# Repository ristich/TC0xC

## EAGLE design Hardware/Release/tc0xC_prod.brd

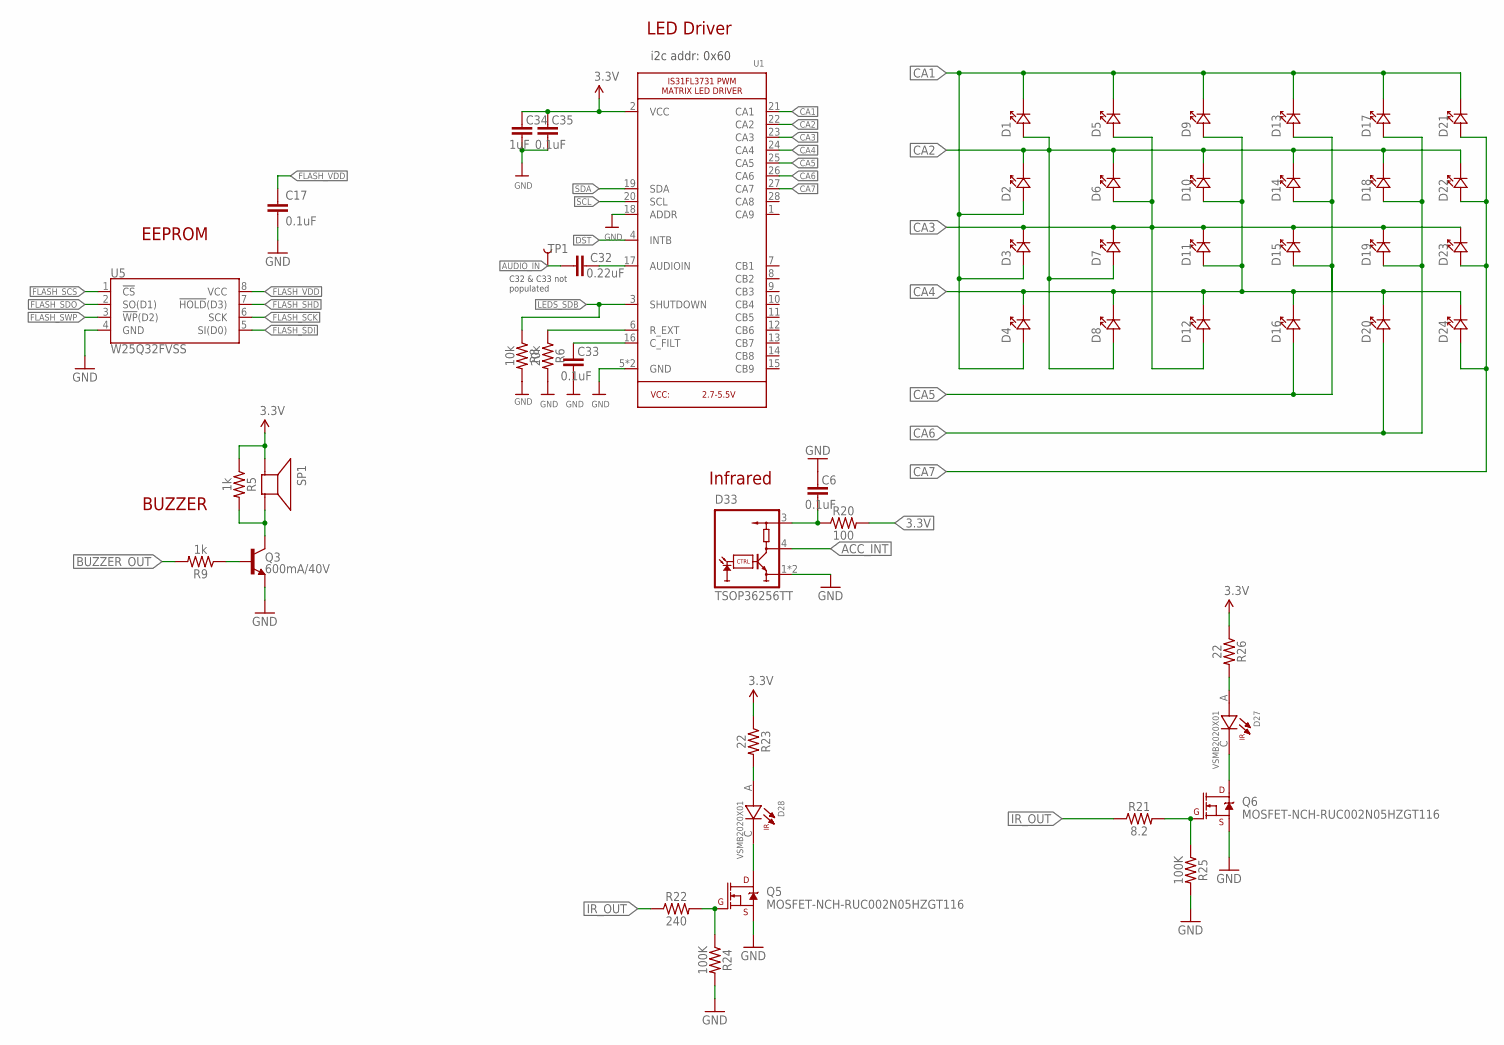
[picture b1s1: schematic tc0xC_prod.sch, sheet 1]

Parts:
C6, C17, C33, C35: 0.1uF; 0603
C32: 0.22uF; 0603
C34: 1uF; 0603
D1, D2, D3, D4, D5, D6, D7, D8, D9, D10, D11, D12, D13, D14, D15, D16, D17, D18, D19, D20, D21, D22, D23, D24: LED-603; SMD-603
D27, D28: VSMB2020X01; DIO_VSMB2020X01
D33: TSOP36256TT; TSOP36256
Q3: 600mA/40V; SOT23-3
Q5, Q6: MOSFET-NCH-RUC002N05HZGT116; SOT-23-3
R5, R9: 1k; 0603
R6: 20k; 0603
R8: 10k; 0603
R20: 100; 0603
R21: 8.2; 0603
R22: 240; 0603
R23, R26: 22; 0603
R24, R25: 100K; 0603
SP1: SPEAKER/PS12; PS12
TP1: TEST-POINT3X5; PAD.03X.05
U1: IS31FL3731QFN; QFN-28_4MM_0.4MM
U5: W25Q32FVSS; SOIC-8

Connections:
3.3V: C34.1, C35.1, R5.1, R20.2, R23.1, R26.1, SP1.P$1 (+), U1.2 (VCC); also elsewhere on the board
ACC_INT: D33.4 (OUT); also elsewhere on the board
AUDIO_IN: C32.1, TP1.P$1
BUZZER_OUT: R9.2; also elsewhere on the board
CA1: D1.P$2 (CATHODE-), D2.P$1 (ANODE+), D3.P$1 (ANODE+), D4.P$1 (ANODE+), D5.P$2 (CATHODE-), D9.P$2 (CATHODE-), D13.P$2 (CATHODE-), D17.P$2 (CATHODE-), D21.P$2 (CATHODE-), U1.21 (CA1)
CA2: D1.P$1 (ANODE+), D2.P$2 (CATHODE-), D6.P$2 (CATHODE-), D7.P$1 (ANODE+), D8.P$1 (ANODE+), D10.P$2 (CATHODE-), D14.P$2 (CATHODE-), D18.P$2 (CATHODE-), D22.P$2 (CATHODE-), U1.22 (CA2)
CA3: D3.P$2 (CATHODE-), D5.P$1 (ANODE+), D6.P$1 (ANODE+), D7.P$2 (CATHODE-), D11.P$2 (CATHODE-), D12.P$1 (ANODE+), D15.P$2 (CATHODE-), D19.P$2 (CATHODE-), D23.P$2 (CATHODE-), U1.23 (CA3)
CA4: D4.P$2 (CATHODE-), D8.P$2 (CATHODE-), D9.P$1 (ANODE+), D10.P$1 (ANODE+), D11.P$1 (ANODE+), D12.P$2 (CATHODE-), D16.P$2 (CATHODE-), D20.P$2 (CATHODE-), D24.P$2 (CATHODE-), U1.24 (CA4)
CA5: D13.P$1 (ANODE+), D14.P$1 (ANODE+), D15.P$1 (ANODE+), D16.P$1 (ANODE+), U1.25 (CA5)
CA6: D17.P$1 (ANODE+), D18.P$1 (ANODE+), D19.P$1 (ANODE+), D20.P$1 (ANODE+), U1.26 (CA6)
CA7: D21.P$1 (ANODE+), D22.P$1 (ANODE+), D23.P$1 (ANODE+), D24.P$1 (ANODE+), U1.27 (CA7)
DST: U1.4 (INTB); also elsewhere on the board
FLASH_SCK: U5.6 (SCK); also elsewhere on the board
FLASH_SCS: U5.1 (!CS!); also elsewhere on the board
FLASH_SDI: U5.5 (SI(D0)); also elsewhere on the board
FLASH_SDO: U5.2 (SO(D1)); also elsewhere on the board
FLASH_SHD: U5.7 (!HOLD!(D3)); also elsewhere on the board
FLASH_SWP: U5.3 (!WP!(D2)); also elsewhere on the board
FLASH_VDD: C17.1, U5.8 (VCC); also elsewhere on the board
GND: C6.1, C17.2, C33.2, C34.2, C35.2, D33.1 (GND), D33.2 (GND), Q3.2 (E), Q5.2 (S), Q6.2 (S), R6.2, R8.2, R24.2, R25.2, U1.5 (GND), U1.18 (ADDR), U1.THERMAL (GND), U5.4 (GND); also elsewhere on the board
IR_OUT: R21.1, R22.1; also elsewhere on the board
LEDS_SDB: R8.1, U1.3 (SHUTDOWN); also elsewhere on the board
unnamed: C33.1, U1.16 (C_FILT)
unnamed: R6.1, U1.6 (R_EXT)
unnamed: Q3.3 (C), R5.2, SP1.P$2 (-)
unnamed: Q6.1 (G), R21.2, R25.1
unnamed: Q5.1 (G), R22.2, R24.1
unnamed: C32.2, U1.17 (AUDIOIN)
unnamed: C6.2, D33.3 (VS), R20.1
unnamed: D28.C, Q5.3 (D)
unnamed: D28.A, R23.2
unnamed: D27.C, Q6.3 (D)
unnamed: D27.A, R26.2
unnamed: Q3.1 (B), R9.1
SCL: U1.20 (SCL); also elsewhere on the board
SDA: U1.19 (SDA); also elsewhere on the board

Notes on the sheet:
i2c addr: 0x60
C32 & C33 not populated
EEPROM
BUZZER
LED Driver
Infrared

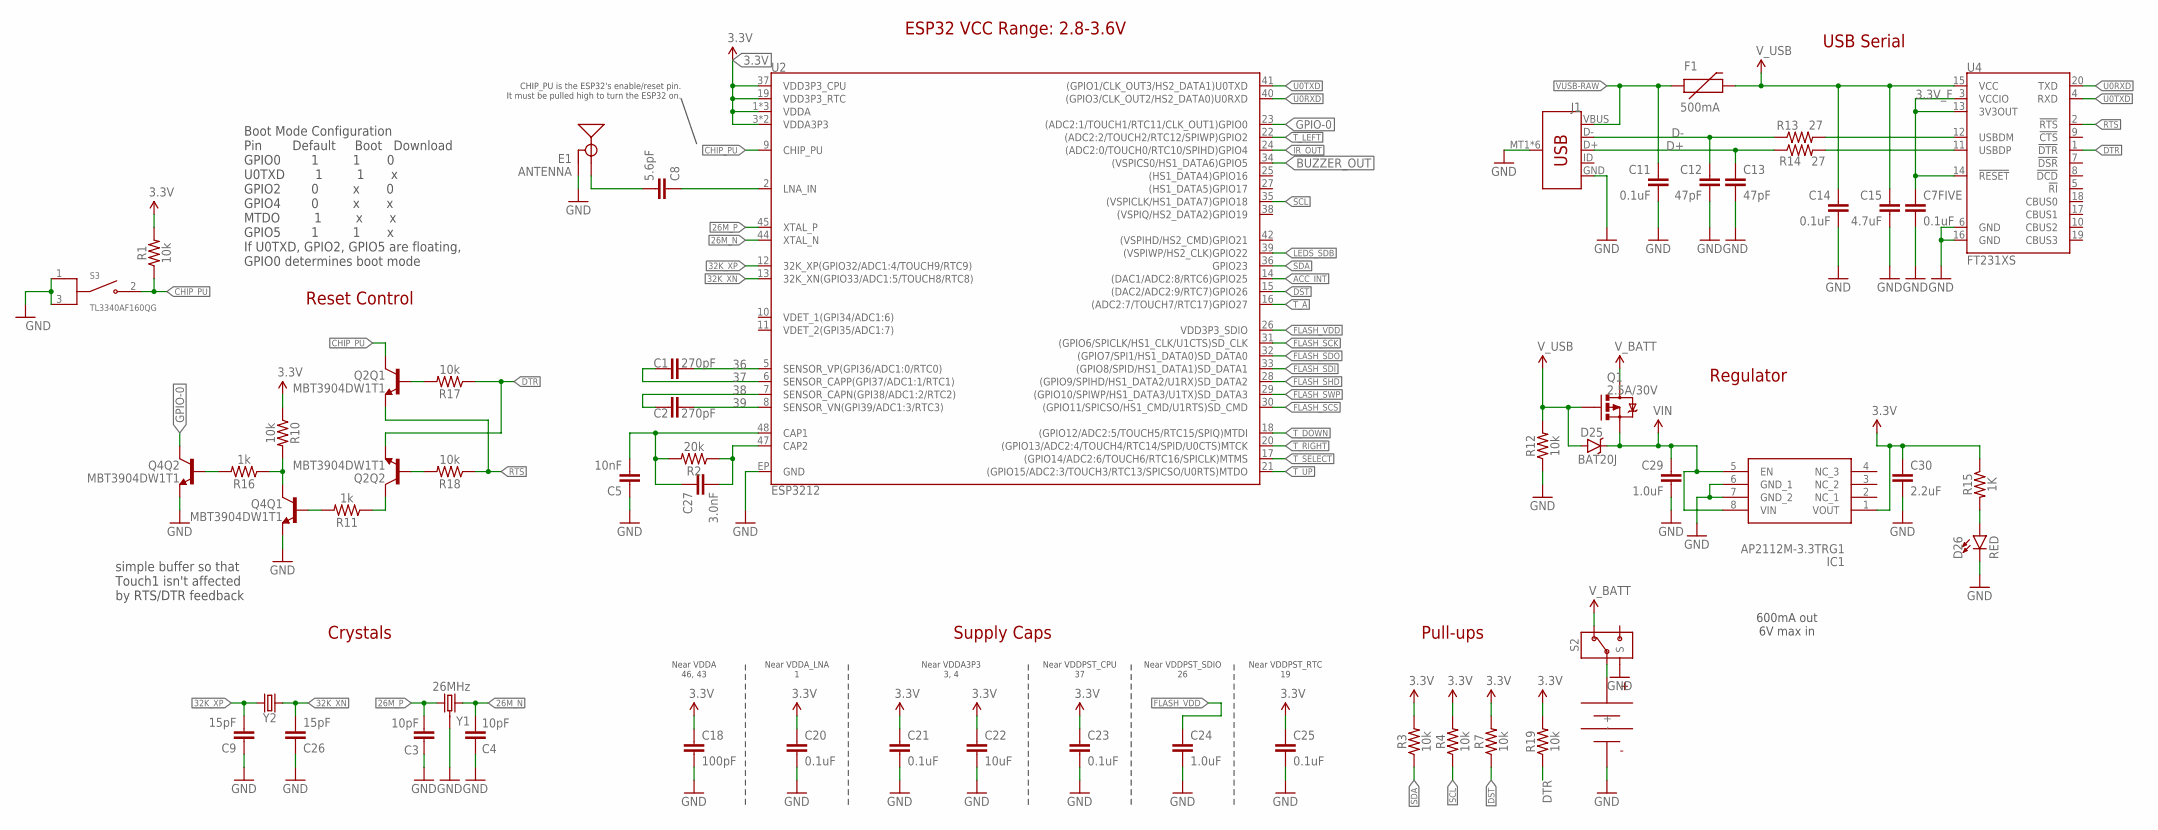
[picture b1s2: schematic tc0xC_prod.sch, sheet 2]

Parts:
C1, C2: 270pF; 0603
C3, C4: 10pF; 0603
C5: 10nF; 0603
C7FIVE, C11, C14, C20, C21, C23, C25: 0.1uF; 0603
C8: 5.6pF; 0603
C9, C26: 15pF; 0603
C12, C13: 47pF; 0603
C15: 4.7uF; 0603
C18: 100pF; 0603
C22: 10uF; 0603
C24: 1.0uF; 0603
C27: 3.0nF; 0603
C29: 1.0uF; 0805
C30: 2.2uF; 0603
D25: BAT20J; SOD-323
D26: RED; LED-0603@1
E1: ANTENNA; TRACE_ANTENNA_2.4GHZ_25.7MM_TUNED
F1: 500mA; PTC-1206
G2: KEYSTONE_2479
IC1: AP2112M-3.3TRG1; SOIC127P600X170-8N
J1: USB_MICRO-B; USB-MICROB-10118192
Q1: 2.5A/30V; SOT23-3@1
Q2, Q4: MBT3904DW1T1; SC70-6
R1, R3, R4, R7, R10, R12, R17, R18, R19: 10k; 0603
R2: 20k; 0603
R11, R16: 1k; 0603
R13, R14: 27; 0603
R15: 1K; 0603
S2: CUS-12B; CUS-12_SPDT
S3: TL3340AF160QG; SW_TL3340AF160QG
U2: ESP3212; QFN48-0.4MM
U4: FT231XS; SSOP20_L
Y1: 26MHz; CRYSTAL-SMD-3.2X2.5
Y2: 32.768kHz; FC-12M

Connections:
3.3V: C18.1, C20.1, C21.1, C22.1, C23.1, C25.1, C30.1, IC1.1 (VOUT), R1.2, R3.2, R4.2, R7.2, R10.1, R15.1, R19.2, U2.1 (VDDA), U2.3 (VDDA3P3), U2.4 (VDDA3P3), U2.19 (VDD3P3_RTC), U2.37 (VDD3P3_CPU), U2.43 (VDDA), U2.46 (VDDA); also elsewhere on the board
3.3V_F: C7FIVE.1, U4.3 (VCCIO), U4.13 (3V3OUT), U4.14 (!RESET)
26M_N: C4.2, U2.44 (XTAL_N), Y1.3 (2)
26M_P: C3.2, U2.45 (XTAL_P), Y1.1
32K_XN: C26.2, U2.13 (32K_XN(GPIO33/ADC1:5/TOUCH8/RTC8)), Y2.2
32K_XP: C9.2, U2.12 (32K_XP(GPIO32/ADC1:4/TOUCH9/RTC9)), Y2.1
36: C1.2, U2.5 (SENSOR_VP(GPI36/ADC1:0/RTC0))
37: C1.1, U2.6 (SENSOR_CAPP(GPI37/ADC1:1/RTC1))
38: C2.1, U2.7 (SENSOR_CAPN(GPI38/ADC1:2/RTC2))
39: C2.2, U2.8 (SENSOR_VN(GPI39/ADC1:3/RTC3))
ACC_INT: U2.14 ((DAC1/ADC2:8/RTC6)GPIO25); also elsewhere on the board
BUZZER_OUT: U2.34 ((VSPICS0/HS1_DATA6)GPIO5); also elsewhere on the board
CAP_10N: C5.2, C27.1, R2.2, U2.48 (CAP1)
CHIP_PU: Q2.3 (C), R1.1, S3.2 (NO), U2.9 (CHIP_PU)
D+: C13.1, J1.D+, R14.1
D-: C12.1, J1.D-, R13.1
DST: R7.1, U2.15 ((DAC2/ADC2:9/RTC7)GPIO26); also elsewhere on the board
DTR: Q2.1 (E), R17.1, R19.1, U4.1 (!DTR)
FLASH_SCK: U2.31 ((GPIO6/SPICLK/HS1_CLK/U1CTS)SD_CLK); also elsewhere on the board
FLASH_SCS: U2.30 ((GPIO11/SPICSO/HS1_CMD/U1RTS)SD_CMD); also elsewhere on the board
FLASH_SDI: U2.33 ((GPIO8/SPID/HS1_DATA1)SD_DATA1); also elsewhere on the board
FLASH_SDO: U2.32 ((GPIO7/SPI1/HS1_DATA0)SD_DATA0); also elsewhere on the board
FLASH_SHD: U2.28 ((GPIO9/SPIHD/HS1_DATA2/U1RX)SD_DATA2); also elsewhere on the board
FLASH_SWP: U2.29 ((GPIO10/SPIWP/HS1_DATA3/U1TX)SD_DATA3); also elsewhere on the board
FLASH_VDD: C24.1, U2.26 (VDD3P3_SDIO); also elsewhere on the board
GND: C3.1, C4.1, C5.1, C7FIVE.2, C9.1, C11.2, C12.2, C13.2, C14.2, C15.2, C18.2, C20.2, C21.2, C22.2, C23.2, C24.2, C25.2, C26.1, C29.2, C30.2, D26.C, E1.GND, E1.GND2 (GND), G2.-, IC1.6 (GND_1), IC1.7 (GND_2), J1.GND, J1.MT1 (SHIELD), J1.MT2 (SHIELD), J1.MT3 (SHIELD), J1.MT4 (SHIELD), J1.P$1 (SHIELD), J1.P$2 (SHIELD), Q4.1 (E), Q4.4 (E), R12.1, S2.P$4 (S), S2.P$5 (S), S2.P$6 (S), S2.P$7 (S), S3.1 (COM_1), S3.3 (COM_2), U2.EP (GND), U4.6 (GND), U4.16 (GND), Y1.2 (GND), Y1.4 (GND); also elsewhere on the board
GPIO-0: Q4.6 (C), U2.23 ((ADC2:1/TOUCH1/RTC11/CLK_OUT1)GPIO0)
IR_OUT: U2.24 ((ADC2:0/TOUCH0/RTC10/SPIHD)GPIO4); also elsewhere on the board
LEDS_SDB: U2.39 ((VSPIWP/HS2_CLK)GPIO22); also elsewhere on the board
LNA_IN: C8.1, U2.2 (LNA_IN)
unnamed: C27.2, R2.1, U2.47 (CAP2)
unnamed: R13.2, U4.12 (USBDM)
unnamed: R14.2, U4.11 (USBDP)
unnamed: Q4.2 (B), R16.2
unnamed: Q2.5 (B), R17.2
unnamed: Q2.2 (B), R18.2
unnamed: Q4.3 (C), R10.2, R16.1
unnamed: Q4.5 (B), R11.2
unnamed: Q2.6 (C), R11.1
unnamed: G2.+, S2.P$2 (1)
unnamed: D26.A, R15.2
RTS: Q2.4 (E), R18.1, U4.2 (!RTS)
SCL: R4.1, U2.35 ((VSPICLK/HS1_DATA7)GPIO18); also elsewhere on the board
SDA: R3.1, U2.36 (GPIO23); also elsewhere on the board
TRACE_ANT: C8.2, E1.ANT (SIGNAL)
T_A: U2.16 ((ADC2:7/TOUCH7/RTC17)GPIO27)
T_DOWN: U2.18 ((GPIO12/ADC2:5/TOUCH5/RTC15/SPIQ)MTDI)
T_LEFT: U2.22 ((ADC2:2/TOUCH2/RTC12/SPIWP)GPIO2)
T_RIGHT: U2.20 ((GPIO13/ADC2:4/TOUCH4/RTC14/SPID/U0CTS)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)
T_SELECT: U2.17 ((GPIO14/ADC2:6/TOUCH6/RTC16/SPICLK)MTMS)
T_UP: U2.21 ((GPIO15/ADC2:3/TOUCH3/RTC13/SPICSO/U0RT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)
U0RXD: U2.40 ((GPIO3/CLK_OUT2/HS2_DATA0)U0RXD), U4.20 (TXD)
U0TXD: U2.41 ((GPIO1/CLK_OUT3/HS2_DATA1)U0TXD), U4.4 (RXD)
VIN: C29.1, D25.C, IC1.5 (EN), IC1.8 (VIN), Q1.2 (S)
VUSB-RAW: C11.1, F1.1, J1.VBUS
V_BATT: Q1.3 (D), S2.P$1 (2)
V_USB: C14.1, C15.1, D25.A, F1.2, Q1.1 (G), R12.2, U4.15 (VCC)

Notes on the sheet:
Near VDDA 46, 43
Near VDDA_LNA 1
Near VDDA3P3 3, 4
Near VDDPST_CPU 37
Near VDDPST_SDIO 26
Near VDDPST_RTC 19
ESP32 VCC Range: 2.8-3.6V
CHIP_PU is the ESP32's enable/reset pin. It must be pulled high to turn the ESP32 on.
Supply Caps
Reset Control
Crystals
600mA out 6V max in
Regulator
USB Serial
Boot Mode Configuration Pin Default Boot Download GPIO0 1 1 0 U0TXD 1 1 x GPIO2 0 x 0 GPIO4 0 x x MTDO 1 x x GPIO5 1 1 x If U0TXD, GPIO2, GPIO5 are floating, GPIO0 determines boot mode
Pull-ups
simple buffer so that Touch1 isn't affected by RTS/DTR feedback

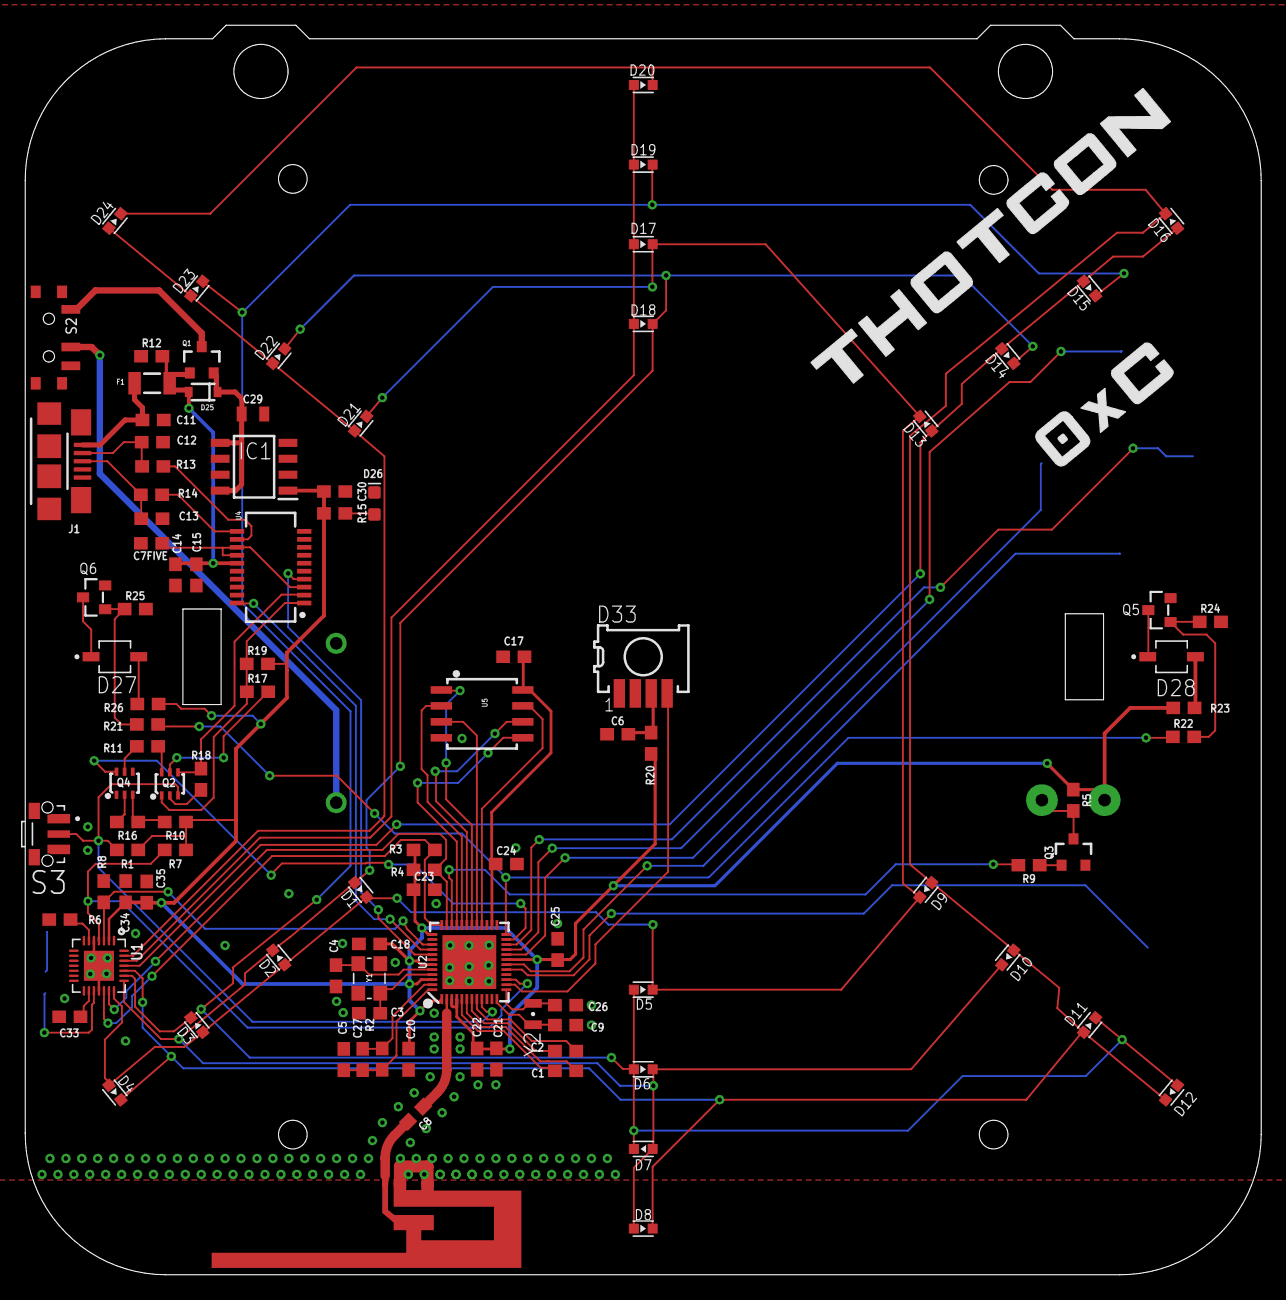
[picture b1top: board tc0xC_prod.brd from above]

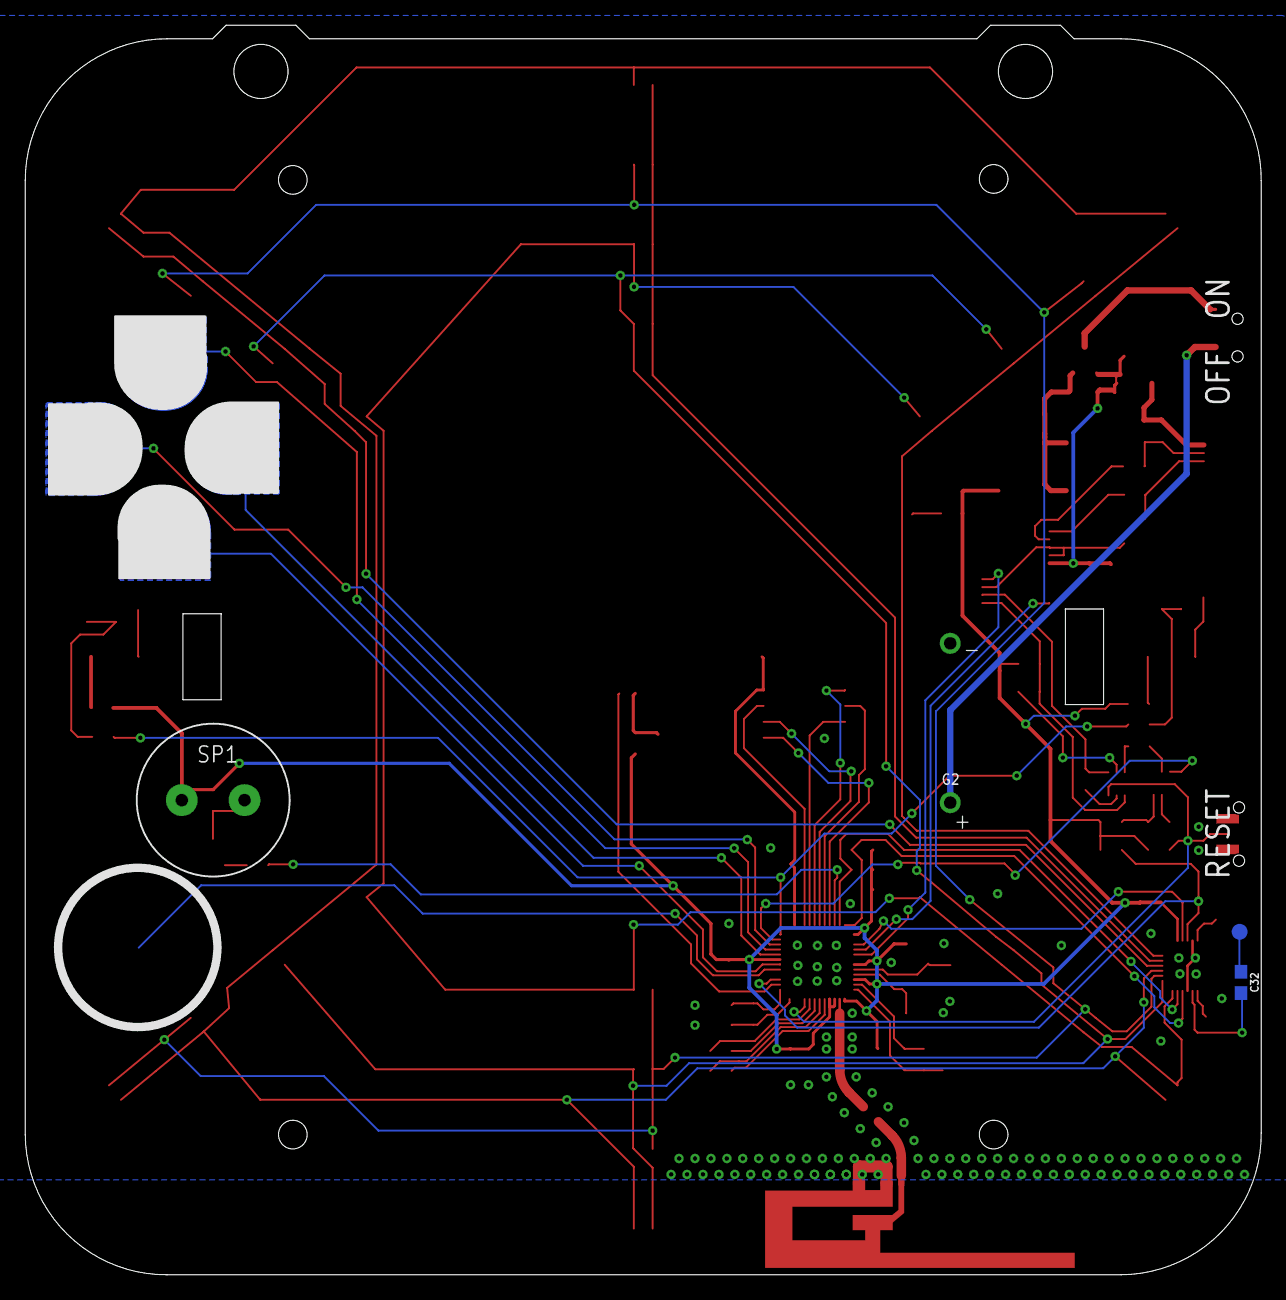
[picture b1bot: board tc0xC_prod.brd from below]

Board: 2 copper layers, 98.6 x 99.6 mm, 106 parts (4 on the bottom side), 71 nets.

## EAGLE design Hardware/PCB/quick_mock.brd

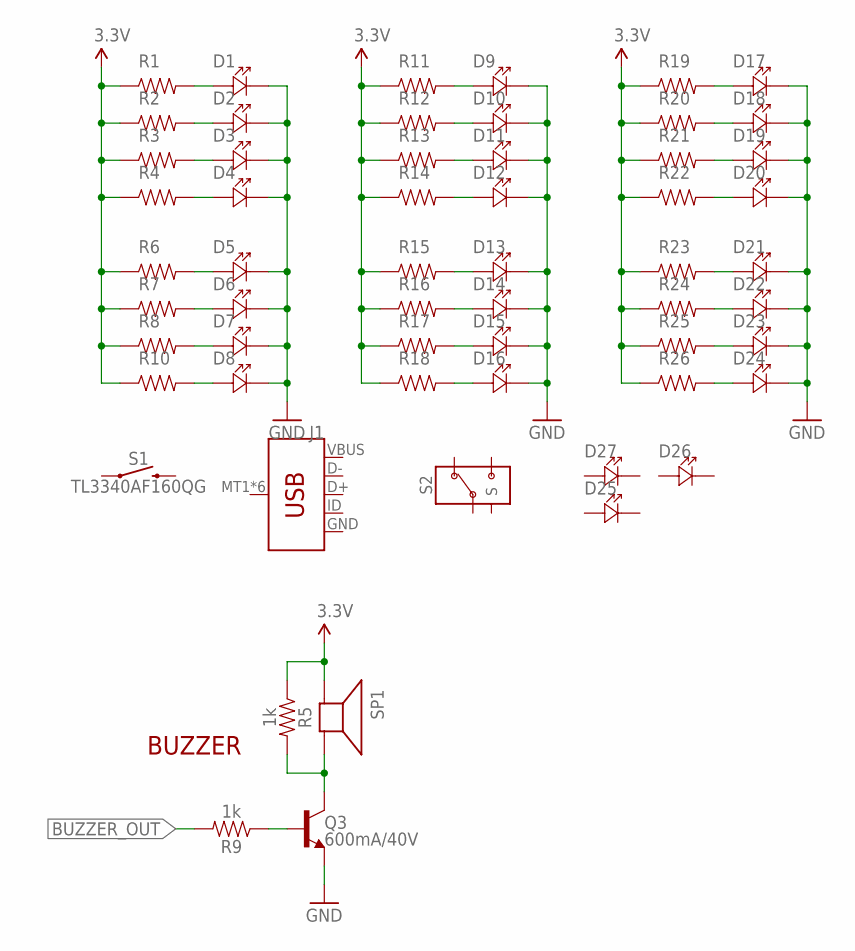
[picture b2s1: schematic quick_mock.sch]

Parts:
D1, D2, D3, D4, D5, D6, D7, D8, D9, D10, D11, D12, D13, D14, D15, D16, D17, D18, D19, D20, D21, D22, D23, D24, D26: LED-603; SMD-603
D25, D27: VSMB2020X01; GULL-WING-2.3MM
J1: USB_MICRO-B; USB-MICROB-10118192
Q3: 600mA/40V; SOT23-3
R1, R2, R3, R4, R6, R7, R8, R10, R11, R12, R13, R14, R15, R16, R17, R18, R19, R20, R21, R22, R23, R24, R25, R26: RESISTOR-603; SMD-603
R5, R9: 1k; 0603
S1: TL3340AF160QG; 3PIN_GULLWING_4.0X3.3MM
S2: CUS-12B; CUS-12_SPDT
SP1: SPEAKER/PS12; PS12

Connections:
3.3V: R1.1, R2.1, R3.1, R4.1, R5.1, R6.1, R7.1, R8.1, R10.1, R11.1, R12.1, R13.1, R14.1, R15.1, R16.1, R17.1, R18.1, R19.1, R20.1, R21.1, R22.1, R23.1, R24.1, R25.1, R26.1, SP1.P$1 (+)
BUZZER_OUT: R9.2
GND: D1.P$2 (CATHODE-), D2.P$2 (CATHODE-), D3.P$2 (CATHODE-), D4.P$2 (CATHODE-), D5.P$2 (CATHODE-), D6.P$2 (CATHODE-), D7.P$2 (CATHODE-), D8.P$2 (CATHODE-), D9.P$2 (CATHODE-), D10.P$2 (CATHODE-), D11.P$2 (CATHODE-), D12.P$2 (CATHODE-), D13.P$2 (CATHODE-), D14.P$2 (CATHODE-), D15.P$2 (CATHODE-), D16.P$2 (CATHODE-), D17.P$2 (CATHODE-), D18.P$2 (CATHODE-), D19.P$2 (CATHODE-), D20.P$2 (CATHODE-), D21.P$2 (CATHODE-), D22.P$2 (CATHODE-), D23.P$2 (CATHODE-), D24.P$2 (CATHODE-), J1.GND, Q3.2 (E)
unnamed: D1.P$1 (ANODE+), R1.2
unnamed: D2.P$1 (ANODE+), R2.2
unnamed: Q3.3 (C), R5.2, SP1.P$2 (-)
unnamed: D3.P$1 (ANODE+), R3.2
unnamed: D4.P$1 (ANODE+), R4.2
unnamed: D5.P$1 (ANODE+), R6.2
unnamed: D6.P$1 (ANODE+), R7.2
unnamed: D7.P$1 (ANODE+), R8.2
unnamed: D8.P$1 (ANODE+), R10.2
unnamed: D9.P$1 (ANODE+), R11.2
unnamed: D10.P$1 (ANODE+), R12.2
unnamed: D11.P$1 (ANODE+), R13.2
unnamed: D12.P$1 (ANODE+), R14.2
unnamed: D13.P$1 (ANODE+), R15.2
unnamed: D14.P$1 (ANODE+), R16.2
unnamed: D15.P$1 (ANODE+), R17.2
unnamed: D16.P$1 (ANODE+), R18.2
unnamed: D24.P$1 (ANODE+), R26.2
unnamed: D23.P$1 (ANODE+), R25.2
unnamed: D22.P$1 (ANODE+), R24.2
unnamed: D21.P$1 (ANODE+), R23.2
unnamed: Q3.1 (B), R9.1
unnamed: D20.P$1 (ANODE+), R22.2
unnamed: D19.P$1 (ANODE+), R21.2
unnamed: D18.P$1 (ANODE+), R20.2
unnamed: D17.P$1 (ANODE+), R19.2
VBUS: J1.VBUS

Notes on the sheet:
BUZZER

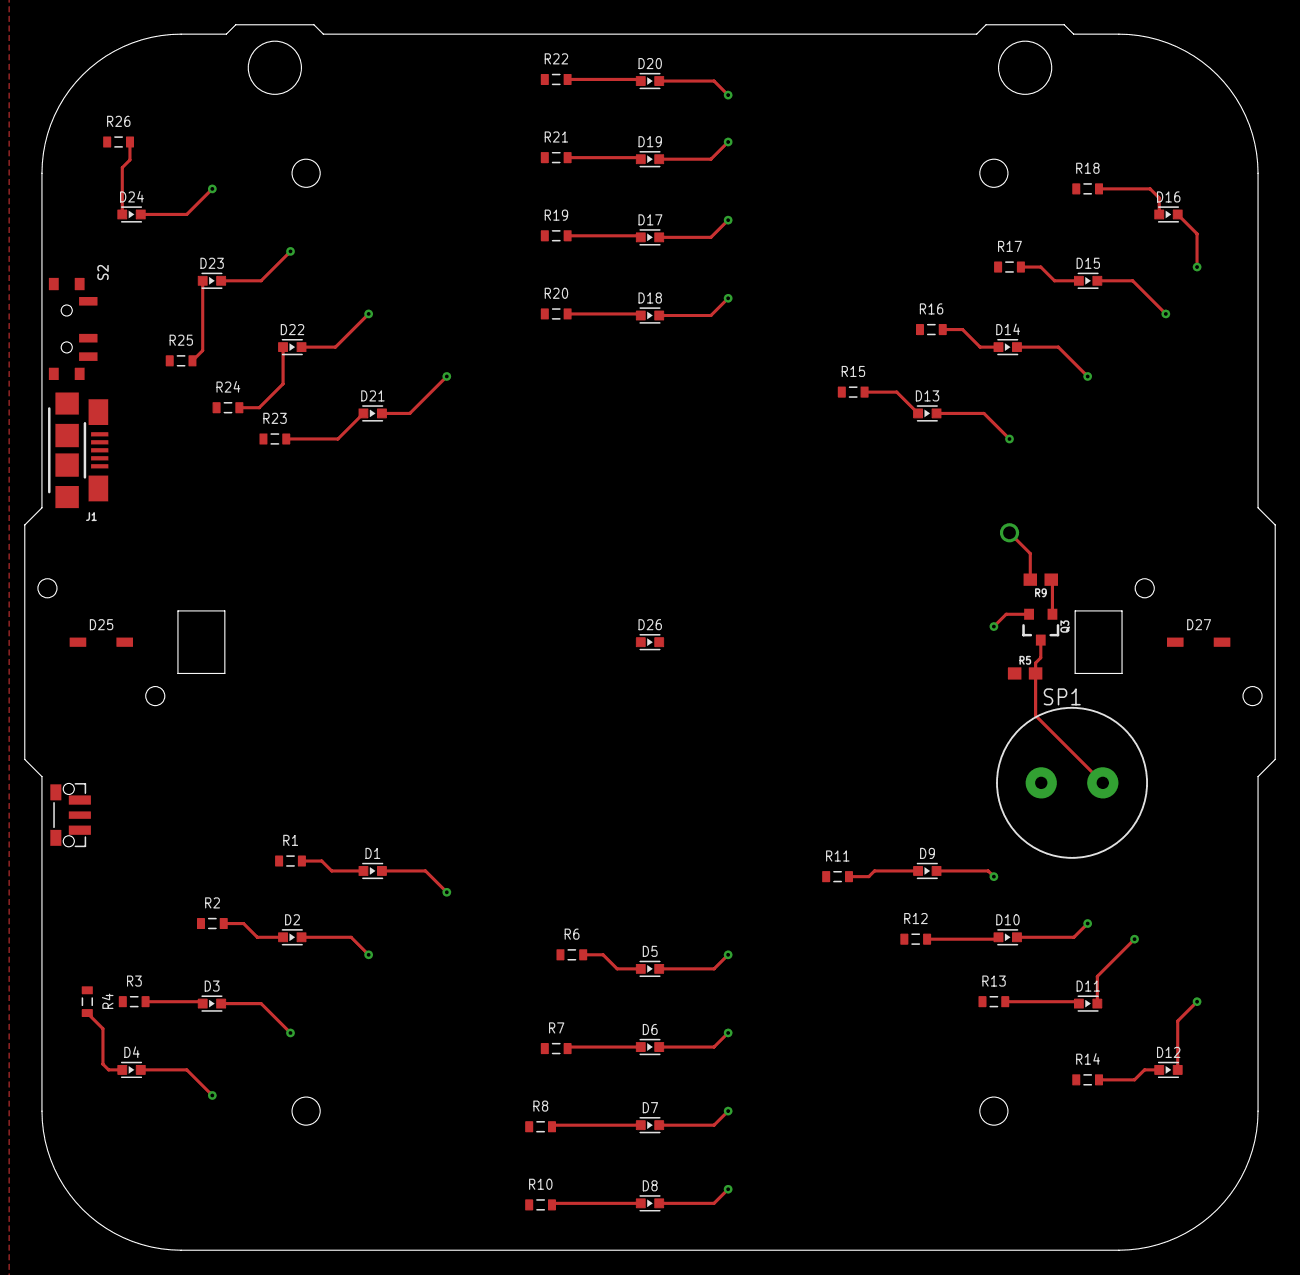
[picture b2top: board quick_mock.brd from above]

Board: 2 copper layers, 101.6 x 99.6 mm, 58 parts (0 on the bottom side), 28 nets.

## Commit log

2023-01-05 add initial designs for PCB and housing
2023-01-10 modify inner design for easier injection molding. prepare files for submitting for quotes.
2023-02-28 add lenses to housing. update PCB dimensions and cutouts to match.
2023-03-03 ripped up prototype
2023-03-04 cleaned ripped up prototype
2023-03-06 matrixed LEDs
2023-03-07 adjust hole sizes. replace emitter LEDs
2023-03-08 add keep outs
2023-03-08 remove a few remnant markers
2023-03-08 merged tKeepOut and drills
2023-03-10 right angle momentary placement
2023-03-11 double push rip up
2023-03-11 mirror of batt and switch fix complete
2023-03-11 move switches. add two types of lanyard mounting
2023-03-13 adjust lanyard holes. prep mock PCB for fab.
2023-03-13 routed
2023-03-14 routed with polys
2023-03-16 adjust LED placement. adjust hole and dimension placement.
2023-03-19 adjust dimensions for better fitting for plastics
2023-03-27 added Release directories
2023-03-29 updates for new housing design
2023-03-31 add silk
2023-04-01 add silk. update layout to fit plastics. minor adjustments to layout.
2023-04-04 update cutouts and keepout. minor routing adjustments.
2023-04-05 small layout adjustments
2023-04-05 updated dimension around lanyard holes
2023-04-06 test sketches
2023-04-06 Review CAMS, Art, Schematic Updates - Pre final route
2023-04-07 Release package and test firmwares
2023-04-08 Hardware and Art dirs
2023-04-10 add 3D models for parts
2023-04-27 add RTOS firmware.
2023-04-29 move led control to its own files.
2023-04-29 move led object declaration to TC0xC_RTOS.ino.
2023-04-29 add commands for controlling leds from cli.
2023-04-29 modify cli to use Badge_Object instance.
2023-04-29 add hal.h
2023-04-30 bring in led driver autoplay and use that for repetitive led control. add a sempaphore for led update signalling.
2023-05-01 add routine to interrupt led pattern to show new pattern.
2023-05-02 switch to using hardware timer for message alarm.
2023-05-03 add basic letter to led translation.
2023-05-04 add string to led display conversion.
2023-05-04 fix delay
2023-05-04 add support for more than two messages.
2023-05-05 started gold project folder
2023-05-06 sounds and wifi / IRC
2023-05-06 trigger LEDs with button press.
2023-05-06 change button press to use xnotify.
2023-05-07 IR objects and UUIDing
2023-05-07 move touch checking to its own files.
2023-05-07 add konami code check.
2023-05-07 add button class for aggregating button info.
2023-05-07 add comments for check_konami.
2023-05-07 add audio playback functionality.
2023-05-07 use notify value to set audio and led playback. asign notes to buttons.
2023-05-08 move touch operations to its own task. fix ledc initialization error.
2023-05-09 change audio so that a new song will interrupt a currently playing song. add contra stage complete and rick roll songs.
2023-05-09 blend of tasks and tag modules plus network functions
2023-05-10 fix audio playback issues.
2023-05-10 change cli led updates to happen wi th xnotify instead of binary semaphore.
2023-05-10 stabilized touch for now
2023-05-12 add space to message display
2023-05-12 add boot led sequence.
2023-05-12 ir task stable plus current build
2023-05-13 add cli led pattern command. add more led patterns.
2023-05-13 add CLI hidden command indicator. add flag command.
2023-05-13 adjust help command to print total number of led modes.
2023-05-14 add buffer overflow opportunity
2023-05-14 make flag command only accessible by buffer overflow.
2023-05-14 flag cleanup
2023-05-14 add settings saving
2023-05-14 final rtos path merges to gold
2023-05-15 ir got stomped, placed it back
2023-05-18 code at flash
2023-05-18 backend
2023-05-23 post conference commit including backened and activity databases and logs
2023-05-23 removed dupe folders
2023-05-23 docs

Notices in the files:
parts and their libraries:
SparkFun-Connectors-new: Licensing: Creative Commons ShareAlike 4.0 International - https://creativecommons.org/licenses/by-sa/4.0
SparkFun-DigitalIC: Licensing: CC v3.0 Share-Alike You are welcome to use this library for commercial purposes.
